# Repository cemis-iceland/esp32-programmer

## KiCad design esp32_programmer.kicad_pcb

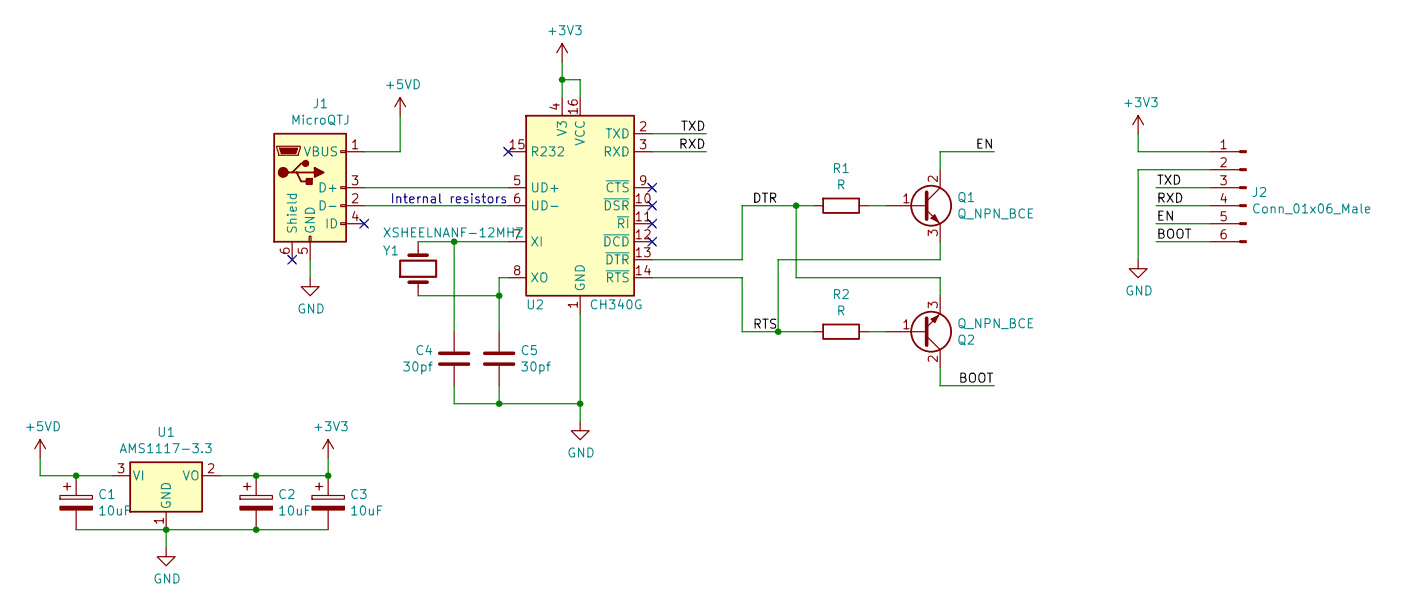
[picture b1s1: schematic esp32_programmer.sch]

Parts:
C1, C2, C3: 10uF; CP_EIA-3216-18_Kemet-A
C4, C5: 30pf; C_0603_1608Metric
J1: MicroQTJ; USB_MicroQTJ
J2: Conn_01x06_Male; PinHeader_1x06_P2.54mm_Vertical
Q1, Q2: Q_NPN_BCE; SOT-23
R1, R2: R; R_0603_1608Metric
U1: AMS1117-3.3; SOT-223-3_TabPin2
U2: CH340G; SOIC-16_3.9x9.9mm_P1.27mm
Y1: XSHEELNANF-12MHZ; XTAL_XSHEELNANF-12MHZ

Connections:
+3V3: C2.1, C3.1, J2.1, U1.2 (VO), U2.4 (V3), U2.16 (VCC)
+5VD: C1.1, J1.1 (VBUS), U1.3 (VI)
/BOOT: J2.6, Q2.2 (C)
/DTR: Q2.3 (E), R1.2, U2.13 (~DTR)
/EN: J2.5, Q1.2 (C)
/RTS: Q1.3 (E), R2.2, U2.14 (~RTS)
/RXD: J2.4, U2.3 (RXD)
/TXD: J2.3, U2.2 (TXD)
GND: C1.2, C2.2, C3.2, C4.1, C5.2, J1.5 (GND), J2.2, U1.1 (GND), U2.1 (GND)
unnamed: C4.2, U2.7 (XI), Y1.2
unnamed: C5.1, U2.8 (XO), Y1.1
unnamed: J1.2 (D-), U2.6 (UD-)
unnamed: J1.3 (D+), U2.5 (UD+)
unnamed: Q1.1 (B), R1.1
unnamed: Q2.1 (B), R2.1

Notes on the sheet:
Internal resistors

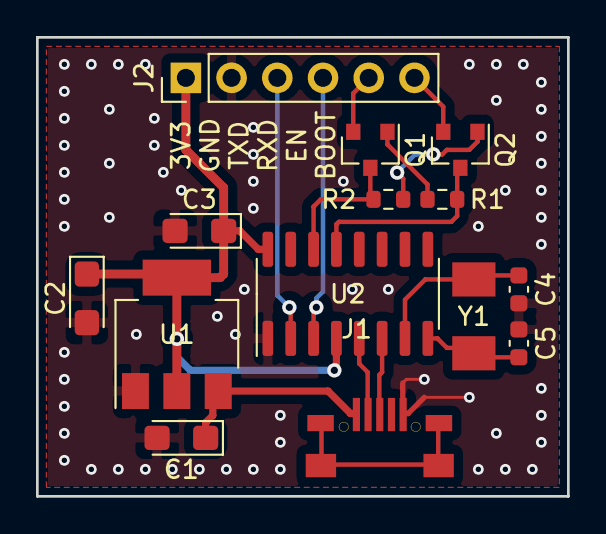
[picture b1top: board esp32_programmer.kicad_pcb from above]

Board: 2 copper layers, 29.5 x 25.5 mm, 14 parts (0 on the bottom side), 15 nets.

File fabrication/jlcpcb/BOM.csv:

Reference, Quantity, Value, Footprint, LCSC
C1 C2 C3 ,3,10uF,Capacitor_Tantalum_SMD:CP_EIA-3216-18_Kemet-A,C7171
C4 C5 ,2,30pf,Capacitor_SMD:C_0603_1608Metric,C22397
J1 ,1,MicroQTJ,esp32-programmer:USB_MicroQTJ,C404968
J2 ,1,Conn_01x06_Male,Connector_PinHeader_2.54mm:PinHeader_1x06_P2.54mm_Vertical,C124380
Q1 Q2 ,2,SS8050,Package_TO_SOT_SMD:SOT-23,C2150
R1 R2 ,2,12k,Resistor_SMD:R_0603_1608Metric,C22790
U1 ,1,AMS1117-3.3,Package_TO_SOT_SMD:SOT-223-3_TabPin2,C6186
U2 ,1,CH340G,Package_SO:SOIC-16_3.9x9.9mm_P1.27mm,C14267
Y1 ,1,XSHEELNANF-12MHZ,esp32-programmer:XTAL_XSHEELNANF-12MHZ,C295065

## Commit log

2021-05-18 initial
2021-05-18 corrected capacitors
2021-05-19 Add project footprints and route PCB
2021-05-19 Design review: Modifications made
    Thickened power traces to 0.4mm
    Changed USB connector footrpint to comply with jlcpcb capabilities.
2021-05-26 Created BOM, Gerbers and pos files. RFM.
